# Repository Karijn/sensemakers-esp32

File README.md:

# sensemakers-esp32
sensemakers esp32 ontwikkelboard

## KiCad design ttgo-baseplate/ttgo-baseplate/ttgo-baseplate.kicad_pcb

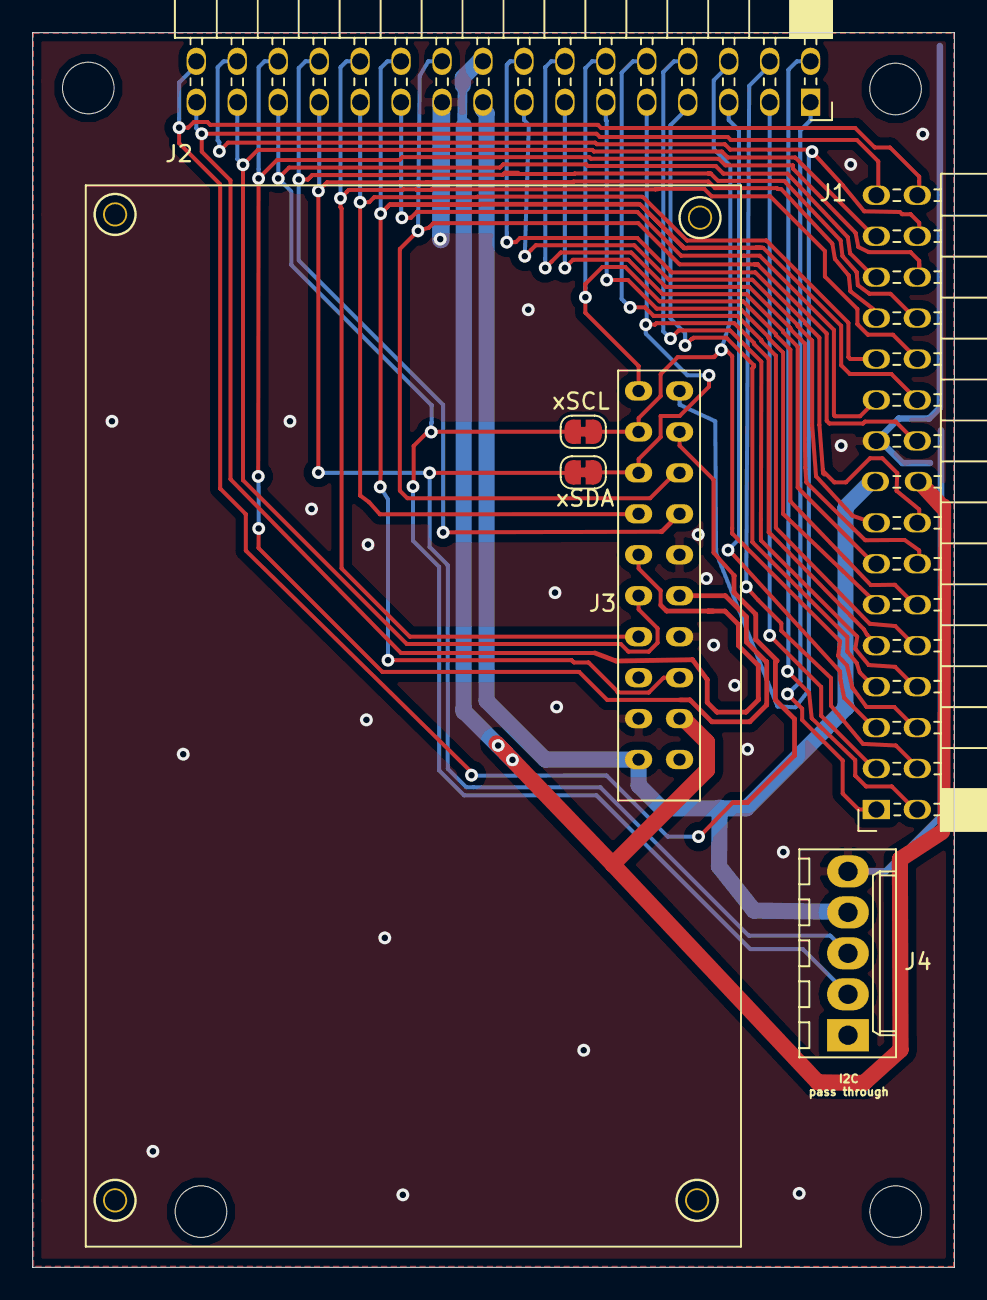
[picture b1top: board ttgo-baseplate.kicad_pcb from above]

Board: 2 copper layers, 57.2 x 76.6 mm, 10 parts (0 on the bottom side), 32 nets.

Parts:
J1, J2: Conn_02x16_Odd_Even; PinSocket_2x16_P2.54mm_Horizontal_oval
J3: Conn_02x10_Odd_Even; ttgo+display
J4: Conn_01x05; Molex_KK-6410-05_05x2.54mm_Straight
MH1, MH2, MH3, MH4: MountingHole; MountingHole_3.2mm_M3
xSCL: SCL; SolderJumper-2_P1.3mm_Bridged_RoundedPad1.0x1.5mm
xSDA: SDA; SolderJumper-2_P1.3mm_Bridged_RoundedPad1.0x1.5mm

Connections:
/3.3V: J1.18, J2.18, J3.12
/5V: J1.17, J2.17, J3.10, J4.4
/GND: J1.19, J2.19, J3.9, J3.14, J3.16, J4.5
/IO00: J1.3, J2.3
/IO02: J1.1, J2.1
/IO04: J1.5, J2.5
/IO05: J1.20, J2.20, J3.18
/IO16: J1.21, J2.21
/IO17: J1.23, J2.23, J3.4
/IO18: J1.26, J2.26, J3.17
/IO19: J1.24, J2.24, J3.7
/IO23: J1.22, J2.22, J3.13
/IO25: J1.11, J2.11
/IO26: J1.28, J2.28, J3.15
/IO27: J1.13, J2.13
/IO32: J1.9, J2.9, J3.3, xSDA.2
/IO33: J1.8, J2.8
/IO34: J1.6, J2.6, J3.2, xSCL.2
/IO35: J1.10, J2.10
/NC1: J1.14, J2.14
/NC2: J1.2, J2.2
/RST: J1.32, J2.32, J3.19
/RXD: J1.29, J2.29, J3.6
/SCL: J1.27, J2.27, J4.2, xSCL.1
/SDA: J1.25, J2.25, J4.3, xSDA.1
/SVN: J1.12, J2.12, J3.1
/SVP: J1.30, J2.30, J3.20
/TCK: J1.16, J2.16
/TD0: J1.15, J2.15
/TDI: J1.7, J2.7
/TMS: J1.4, J2.4
/TXD: J1.31, J2.31, J3.5

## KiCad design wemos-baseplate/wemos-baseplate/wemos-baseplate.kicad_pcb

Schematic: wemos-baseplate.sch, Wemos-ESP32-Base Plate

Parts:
J1: Conn_02x16_Odd_Even; PinHeader_2x16_P2.54mm_Horizontal_oval
J2: Conn_02x16_Odd_Even; PinSocket_2x16_P2.54mm_Horizontal_oval
J3, J4, J5, J6, J9, J10, J11, J12, J13, J14, J15: Conn_01x04; Grove_1x04_oval
J7, J8: Conn_01x04; Grove_1x04
MH1, MH2, MH3, MH4: MountingHole; MountingHole_3.2mm_M3
U1, U2, U3: ESP32-MINI-32; QIP-40_1000_ELL

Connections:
/3.3V: J1.18, J2.18, J3.3, J4.3, J5.3, J6.3, J7.3, J8.3, J9.3, J10.3, J11.3, J12.3, J13.3, J14.3, J15.3, U1.8, U2.8, U3.8
/5V: J1.17, J2.17, U1.13, U2.13, U3.13
/CLK: U1.31, U2.31, U3.31
/CMD: U1.30, U2.30, U3.30
/GND: J1.19, J2.19, J3.4, J4.4, J5.4, J6.4, J7.4, J8.4, J9.4, J10.4, J11.4, J12.4, J13.4, J14.4, J15.4, U1.14, U1.21, U1.40, U2.14, U2.21, U2.40, U3.14, U3.21, U3.40
/IO00: J1.3, J2.3, U1.34, U2.34, U3.34
/IO02: J1.1, J2.1, U1.33, U2.33, U3.33
/IO04: J1.5, J2.5, J13.2, U1.35, U2.35, U3.35
/IO05: J1.20, J2.20, U1.7, U2.7, U3.7
/IO16: J1.21, J2.21, J12.1, U1.15, U2.15, U3.15
/IO17: J1.23, J2.23, J12.2, U1.16, U2.16, U3.16
/IO18: J1.26, J2.26, J10.1, U1.4, U2.4, U3.4
/IO19: J1.24, J2.24, J10.2, U1.5, U2.5, U3.5
/IO23: J1.22, J2.22, U1.6, U2.6, U3.6
/IO25: J1.11, J2.11, J9.2, U1.38, U2.38, U3.38
/IO26: J1.28, J2.28, J9.1, U1.3, U2.3, U3.3
/IO27: J1.13, J2.13, J11.2, U1.39, U2.39, U3.39
/IO32: J1.9, J2.9, J7.2, U1.37, U2.37, U3.37
/IO33: J1.8, J2.8, J7.1, U1.25, U2.25, U3.25
/IO34: J1.6, J2.6, J15.1, U1.26, U2.26, U3.26
/IO35: J1.10, J2.10, J15.2, U1.24, U2.24, U3.24
/NC1: J1.14, J2.14, U1.22, U2.22, U3.22
/NC2: J1.2, J2.2, U1.28, U2.28, U3.28
/RST: J1.32, J2.32, U1.1, U2.1, U3.1
/RXD: J1.29, J2.29, J14.1, U1.19, U2.19, U3.19
/SCL: J1.27, J2.27, J3.1, J4.1, J5.1, J6.1, U1.18, U2.18, U3.18
/SD0: U1.11, U2.11, U3.11
/SD1: U1.32, U2.32, U3.32
/SD2: U1.29, U2.29, U3.29
/SD3: U1.10, U2.10, U3.10
/SDA: J1.25, J2.25, J3.2, J4.2, J5.2, J6.2, U1.17, U2.17, U3.17
/SVN: J1.12, J2.12, J8.2, U1.23, U2.23, U3.23
/SVP: J1.30, J2.30, J8.1, U1.2, U2.2, U3.2
/TCK: J1.16, J2.16, U1.9, U2.9, U3.9
/TD0: J1.15, J2.15, J13.1, U1.12, U2.12, U3.12
/TDI: J1.7, J2.7, U1.36, U2.36, U3.36
/TMS: J1.4, J2.4, J11.1, U1.27, U2.27, U3.27
/TXD: J1.31, J2.31, J14.2, U1.20, U2.20, U3.20

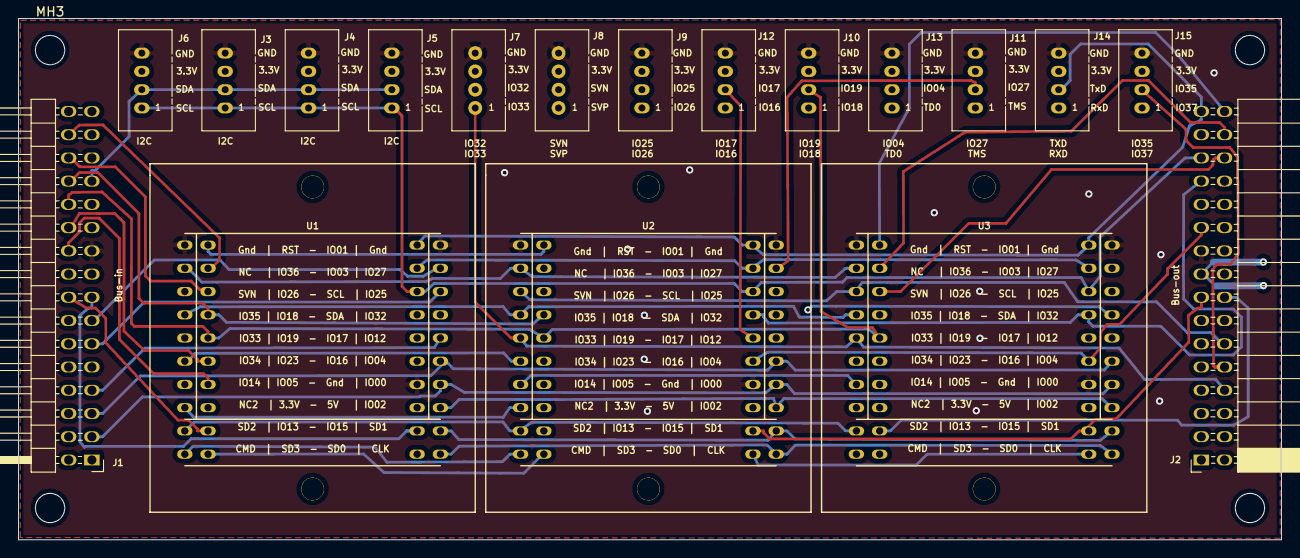
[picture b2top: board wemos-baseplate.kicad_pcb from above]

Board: 4 copper layers, 138.1 x 57.0 mm, 22 parts (0 on the bottom side), 38 nets.

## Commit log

2020-01-31 Initial version
2020-01-31 added library
2020-01-31 footprint OK
    horizontal lines set
2020-02-01 corrected lib
    added spreadsheet with PinMapping
2020-02-01 readme update
2020-02-01 1st print layout with i2c/grove and extention connectors
2020-02-01 versie met 30 pinnen in connector
2020-02-02 added grove connectors
    added labels for grove connectors
    added filled area's for ground and 3v3 plane
2020-02-02 started ttgo-board
    added image
2020-02-02 corrected image
2020-02-02 corrected image path
2020-02-03 new layout with wrove connectors finished
2020-02-03 removed ttgo files
    added .ignore files
2020-02-03 removed backup files
2020-02-03 corrected library, still a few nets on the board to fix
    in2tech library in separate path
2020-02-04 final version before graphics
2020-02-05 updated images
2020-02-05 next try for images
2020-02-05 added mount holes for ttgo board
2020-02-05 changed one plte to 3.3V and one to GND
    removed (to OLD dir) old library
2020-02-05 forgotten files
2020-02-05 added filled zone for +5V
2020-02-06 buildrules changed (but not implemented yet)
2020-02-06 ttgo baseplate rerouted
2020-02-06 gnd en 3v3 panes in center now
2020-02-06 corrected texts
    created gerber files
2020-02-06 removed gerber again
2020-02-06 added gerber to .gitignore
2020-02-07 added
    - artwork
    - pin info
    - ground pane on inner layer
2020-02-07 rotated label
2020-02-08 texts added
    new images for webpage
2020-02-08 new image
2020-02-09 - Revised wemos-base-plate - ground planes to top and bottom - all tracks to 0.3 mm - proper mounting holes in edges - measurements to (not used) front adhesive layer - front sik screen layout change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
2020-02-10 - Adjusted T4 size and drilling holes on footprint - Changed footprint of the TTGO T4 expansion connector to match pn numbering of schematic. - Signals on the TTGO T4 were mirrorred top bottom, corre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
2020-02-11 Added 2 layer print
    added ttgo schema
2020-02-13 finished 2 layer version
